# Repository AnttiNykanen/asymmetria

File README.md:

# ESP8266-based LED dimmer #

This dimmer designed to fit inside a Lival Asymmetria desk lamp. The
plan is to use [LED strips like these][ledstrips] to replace the stock
fluorescent bulb, but other kinds of LEDs should work too, as long as
you adjust the shunt resistor accordingly and don't exceed the 3.3V
regulator's ratings.

## Contents of this directory ##

  * [hardware](./hardware/): Hardware design files
  * [firmware](./firmware/): Firmware source code
  * [doc](./doc/): Documentation
  
## License ##

  * Hardware:
    [CC BY-SA 4.0](https://creativecommons.org/licenses/by-sa/4.0/)
  * Firmware:
    * Files in the user subdirectory:
      [ISC](https://opensource.org/licenses/ISC)
    * Everything else: whatever the files say
 
## The Fine Print ##

Note that owning and/or using homemade radio transmitters, which this thing is, might not be legal for everyone everywhere.

[ledstrips]: http://www.aliexpress.com/item/Ultra-thin-5W-LED-COB-60-Chip-Led-Driving-DRL-Daytime-Running-Light-Lamp-Bar-Strip/32303226004.html

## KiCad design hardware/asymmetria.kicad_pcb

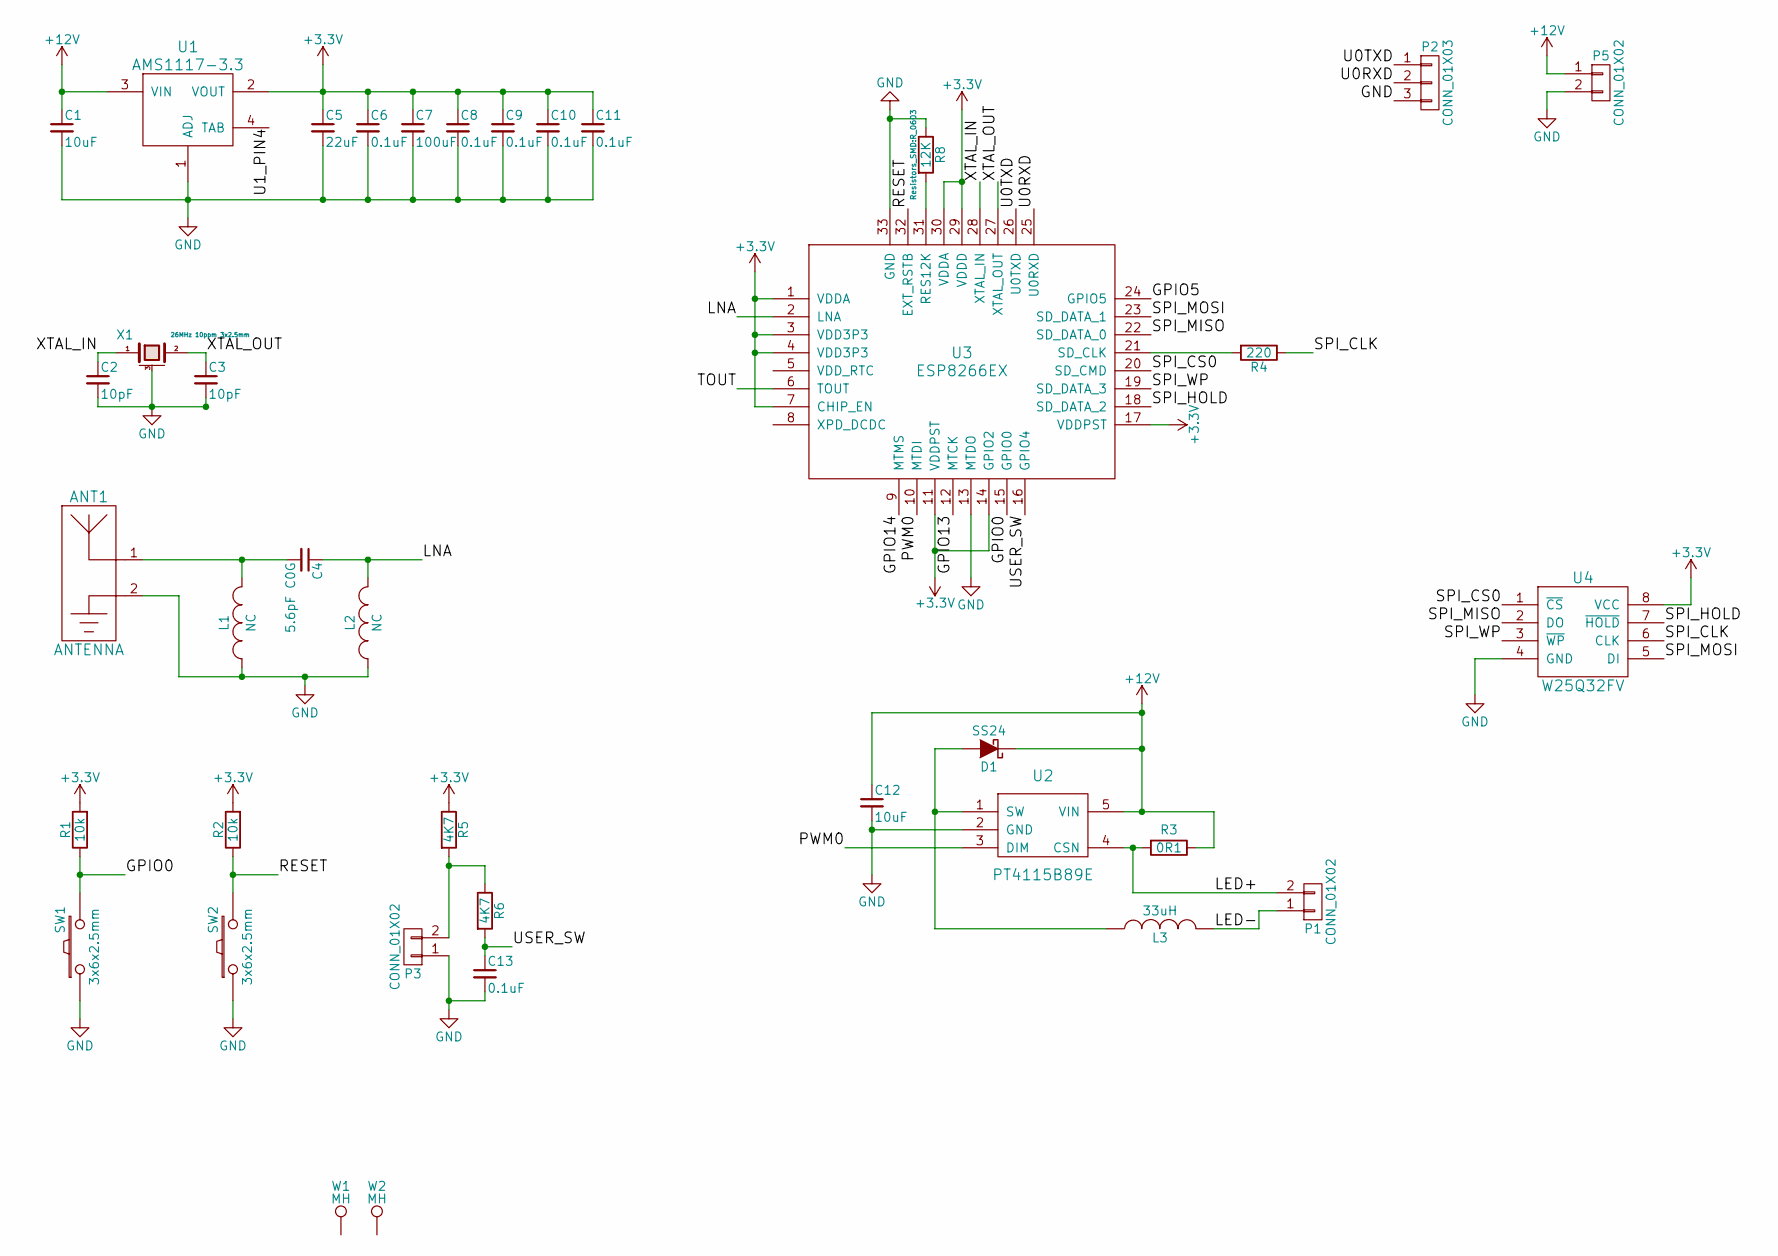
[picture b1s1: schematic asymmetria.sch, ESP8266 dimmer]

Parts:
ANT1: ANTENNA; PCB_IF_ANT_2.4G
C1, C12: 10uF; C_1206
C2, C3: 10pF; C_0603
C4: 5.6pF C0G; C_0603
C5: 22uF; C_1206
C6, C8, C9, C10, C11, C13: 0.1uF; C_0603
C7: 100uF; C_1206
D1: SS24; SMB_Standard
L1, L2: NC; R_0603
L3: 33uH; Choke_SMD_12x12mm_h8mm
P1: CONN_01X02; 5EHDRM-02P
P2: CONN_01X03; Pin_Header_Straight_1x03
P3: CONN_01X02; Pin_Header_Straight_1x02
P5: CONN_01X02; bornier2
R1, R2: 10k; R_0603
R3: 0R1; R_1206
R4: 220; R_0603
R5, R6: 4K7; R_0603
R8: 12K; R_0603
SW1, SW2: 3x6x2.5mm; SPST_3x6x2.5_SMD
U1: AMS1117-3.3; SOT-223
U2: PT4115B89E; SOT89-5_Housing
U3: ESP8266EX; QFN-32-1EP_5x5mm_Pitch0.5mm
U4: W25Q32FV; SOIC-8-208
W1, W2: MH; 1pin
X1: 26MHz 10ppm 3x2.5mm; crystal_FA238-TSX3225

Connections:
+3V3: C5.1, C6.1, C7.1, C8.1, C9.1, C10.1, C11.1, R1.2, R2.2, R5.1, U1.2 (VOUT), U3.1 (VDDA), U3.3 (VDD3P3), U3.4 (VDD3P3), U3.7 (CHIP_EN), U3.11 (VDDPST), U3.14 (GPIO2), U3.17 (VDDPST), U3.29 (VDDD), U3.30 (VDDA), U4.8 (VCC)
+12V: C1.1, C12.1, D1.1 (K), P5.1, R3.1, U1.3 (VIN), U2.5 (VIN)
/GPIO0: R1.1, SW1.2, U3.15 (GPIO0)
/GPIO5: U3.24 (GPIO5)
/GPIO13: U3.12 (MTCK)
/GPIO14: U3.9 (MTMS)
/LED+: P1.2, R3.2, U2.4 (CSN)
/LED-: L3.2, P1.1
/LNA: C4.1, L2.2, U3.2 (LNA)
/PWM0: U2.3 (DIM), U3.10 (MTDI)
/RESET: R2.1, SW2.2, U3.32 (EXT_RSTB)
/SPI_CLK: R4.1, U4.6 (CLK)
/SPI_CS0: U3.20 (SD_CMD), U4.1 (~CS)
/SPI_HOLD: U3.18 (SD_DATA_2), U4.7 (~HOLD)
/SPI_MISO: U3.22 (SD_DATA_0), U4.2 (DO)
/SPI_MOSI: U3.23 (SD_DATA_1), U4.5 (DI)
/SPI_WP: U3.19 (SD_DATA_3), U4.3 (~WP)
/TOUT: U3.6 (TOUT)
/U0RXD: P2.2, U3.25 (U0RXD)
/U0TXD: P2.1, U3.26 (U0TXD)
/U1_PIN4: U1.4 (TAB)
/USER_SW: C13.1, R6.2, U3.16 (GPIO4)
/XTAL_IN: C2.1, U3.28 (XTAL_IN), X1.1
/XTAL_OUT: C3.1, U3.27 (XTAL_OUT), X1.2
GND: ANT1.2, C1.2, C2.2, C3.2, C5.2, C6.2, C7.2, C8.2, C9.2, C10.2, C11.2, C12.2, C13.2, L1.1, L2.1, P2.3, P3.1, P5.2, R8.1, SW1.1, SW2.1, U1.1 (ADJ), U2.2 (GND), U3.13 (MTDO), U3.33 (GND), U4.4 (GND), X1.3 (case)
unnamed: ANT1.1, C4.2, L1.2
unnamed: D1.2 (A), L3.1, U2.1 (SW)
unnamed: P3.2, R5.2, R6.1
unnamed: R4.2, U3.21 (SD_CLK)
unnamed: R8.2, U3.31 (RES12K)

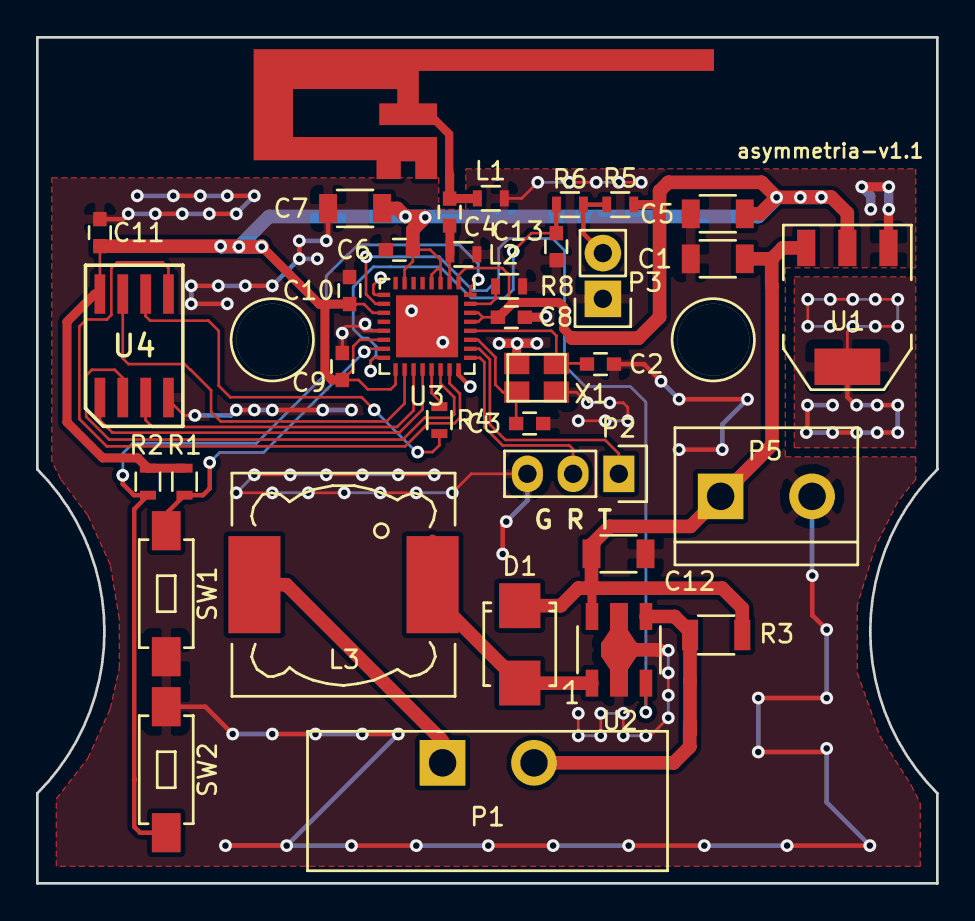
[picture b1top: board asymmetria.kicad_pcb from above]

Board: 2 copper layers, 50.0 x 47.0 mm, 38 parts (0 on the bottom side), 25 nets.

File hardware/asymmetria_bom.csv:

"Note: for the most part these aren't the actual P/N's I've used, but rather what I think would be suitable and is available from suppliers. YMMV.",,,,,,
Reference, Value, Footprint,Manufacturer,Mfg P/N,Location,Status
U3,ESP8266EX,Housings_DFN_QFN:QFN-32-1EP_5x5mm_Pitch0.5mm,Espressif,ESP8266EX,None,ordered
C1,10uF,Capacitors_SMD:C_1206,Yageo,CC1206KKX7R8BB106,None,ordered
C5,22uF,Capacitors_SMD:C_1206,Yageo,CC1206KKX7R6BB226,None,ordered
R8,12K,Resistors_SMD:R_0603,Vishay/Dale,CRCW060312K0FKEA,None,ordered
C6,0.1uF,Capacitors_SMD:C_0603,Yageo,CC0603KRX7R9BB104,01-03-03,in stock
C7,10uF,Capacitors_SMD:C_1206,Yageo,CC1206KKX7R8BB106,None,ordered
C8,0.1uF,Capacitors_SMD:C_0603,Yageo,CC0603KRX7R9BB104,01-03-03,in stock
X1,26MHz 10ppm 3x2.5mm,Crystals_Oscillators_SMD:crystal_FA238-TSX3225,Epson Timing,TSX-3225 26.0000MF09Z-AC3,None,ordered
C2,10pF,Capacitors_SMD:C_0603,Yageo,CC0603GRNPO9BN100,None,ordered
C3,10pF,Capacitors_SMD:C_0603,Yageo,CC0603GRNPO9BN100,None,ordered
C10,0.1uF,Capacitors_SMD:C_0603,Yageo,CC0603KRX7R9BB104,01-03-03,in stock
ANT1,ANTENNA,umetronics:PCB_IF_ANT_2.4G,NA,NA,NA,NA
L1,NC,Resistors_SMD:R_0603,NA,NA,NA,NA
L2,NC,Resistors_SMD:R_0603,NA,NA,NA,NA
C4,5.6pF C0G,Capacitors_SMD:C_0603,Yageo,CC0603CRNPO9BN5R6,None,ordered
SW1,3x6x2.5mm,Buttons_Switches_SMD:SW_SPST_EVQPE1,TE Connectivity,FSMSM,None,ordered
R1,10k,Resistors_SMD:R_0603,Vishay/Dale,CRCW060310K0FKEA,01-01-01,in stock
SW2,3x6x2.5mm,Buttons_Switches_SMD:SW_SPST_EVQPE1,TE Connectivity,FSMSM,None,ordered
R2,10k,Resistors_SMD:R_0603,Vishay/Dale,CRCW060310K0FKEA,01-01-01,in stock
U4,W25Q32FV,umetronics:SOIC-8-208,Winbond,W25Q32FVSSIG,None,ordered
C11,0.1uF,Capacitors_SMD:C_0603,Yageo,CC0603KRX7R9BB104,01-03-03,in stock
R4,220R,Resistors_SMD:R_0603,Vishay/Dale,CRCW0603220RFKEA,None,ordered
U2,PT4115B89E,Housings_SOT-89:SOT89-5_Housing,PowTech,PT4115B89E,None,ordered
R3,0R1,Resistors_SMD:R_1206,Yageo,PT1206FR-070R1L,None,ordered
D1,SS24,Diodes_SMD:SMB_Standard,ON Semiconductor,SS24T3G,None,ordered
L3,33uH,Choke_SMD:Choke_SMD_12x12mm_h8mm,TDK,B82477G4333M,01-07-03,in stock
C12,10uF,Capacitors_SMD:C_1206,Yageo,CC1206KKX7R8BB106,None,ordered
P1,CONN_01X02,umetronics:5EHDRM-02P,Dinkle,5EHDRM-02P,Scrap,in stock
P2,CONN_01X03,Pin_Headers:Pin_Header_Straight_1x03,TE Connectivity,4-103321-5,01-09-01,in stock
P3,CONN_01X02,Pin_Headers:Pin_Header_Straight_1x02,TE Connectivity,5-146278-2,01-09-01,in stock
R5,R,Resistors_SMD:R_0603,,,None,ordered
R6,R,Resistors_SMD:R_0603,,,None,ordered
C13,0.1uF,Capacitors_SMD:C_0603,Yageo,CC0603KRX7R9BB104,01-03-03,in stock
P5,CONN_01X02,Connect:bornier2,TE Connectivity,282837-2,None,ordered
C9,0.1uF,Capacitors_SMD:C_0603,Yageo,CC0603KRX7R9BB104,01-03-03,in stock
U1,AMS1117-3.3,TO_SOT_Packages_SMD:SOT-223,Advanced Monolithic Systems,AMS1117-3.3,01-07-01,in stock
,,15mm dia switch,,,None,ordered

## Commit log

2015-11-21 initial revision
2015-12-04 component checks
2015-12-14 beginnings of firmware, gerbers for hardware
2015-12-15 button ui
2015-12-15 added debounce resistor values
2016-01-13 grounded qfn center pad, increased C7 to 100uF
2016-01-13 updated drill file
2016-01-13 more doxygen comments
2016-01-13 moved bom to doc, added doxyfile
2016-01-13 PCB photo
2016-01-14 group schematic into sections
2016-01-14 more documentation files
2016-01-14 small photo for root dir readme
2016-01-26 edited readme, added user code license
2016-01-26 changed pwm frequency
2016-01-26 comments
2016-01-27 more wifi settings

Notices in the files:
hardware/asymmetria.kicad_pcb:
CC BY 4.0
CC BY 4.0 12/2015
